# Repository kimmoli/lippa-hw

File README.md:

LIPPA
=====

* Powering 7.4V 2.5Ah lipo
* PCB Size 80x50 mm, M3 mounting holes at corners 3.5/3.5
* 4 stepper motor drivers
* 3 servo drivers
* CPU STM32
  * UART for Lidar
  * Debug UART
  * USB VCP
  * 3 timers for servo
  * 4 timers for stepper
  * 4 GPIO to control servo directions
  * 4 GPIO to control servo enables
  * 4 GPIO to control servo microstep modes
  * SPI for PS2 controller

Parts
===== 
* CPU [STM32F417VE](http://www.st.com/content/ccc/resource/technical/document/datasheet/98/9f/89/73/01/b1/48/98/DM00035129.pdf/files/DM00035129.pdf/jcr:content/translations/en.DM00035129.pdf)
* Stepper drivers [DRV8834](http://www.ti.com/lit/ds/symlink/drv8834.pdf)
* Power supply [TPS561201](http://www.ti.com/lit/ds/symlink/tps561201.pdf)

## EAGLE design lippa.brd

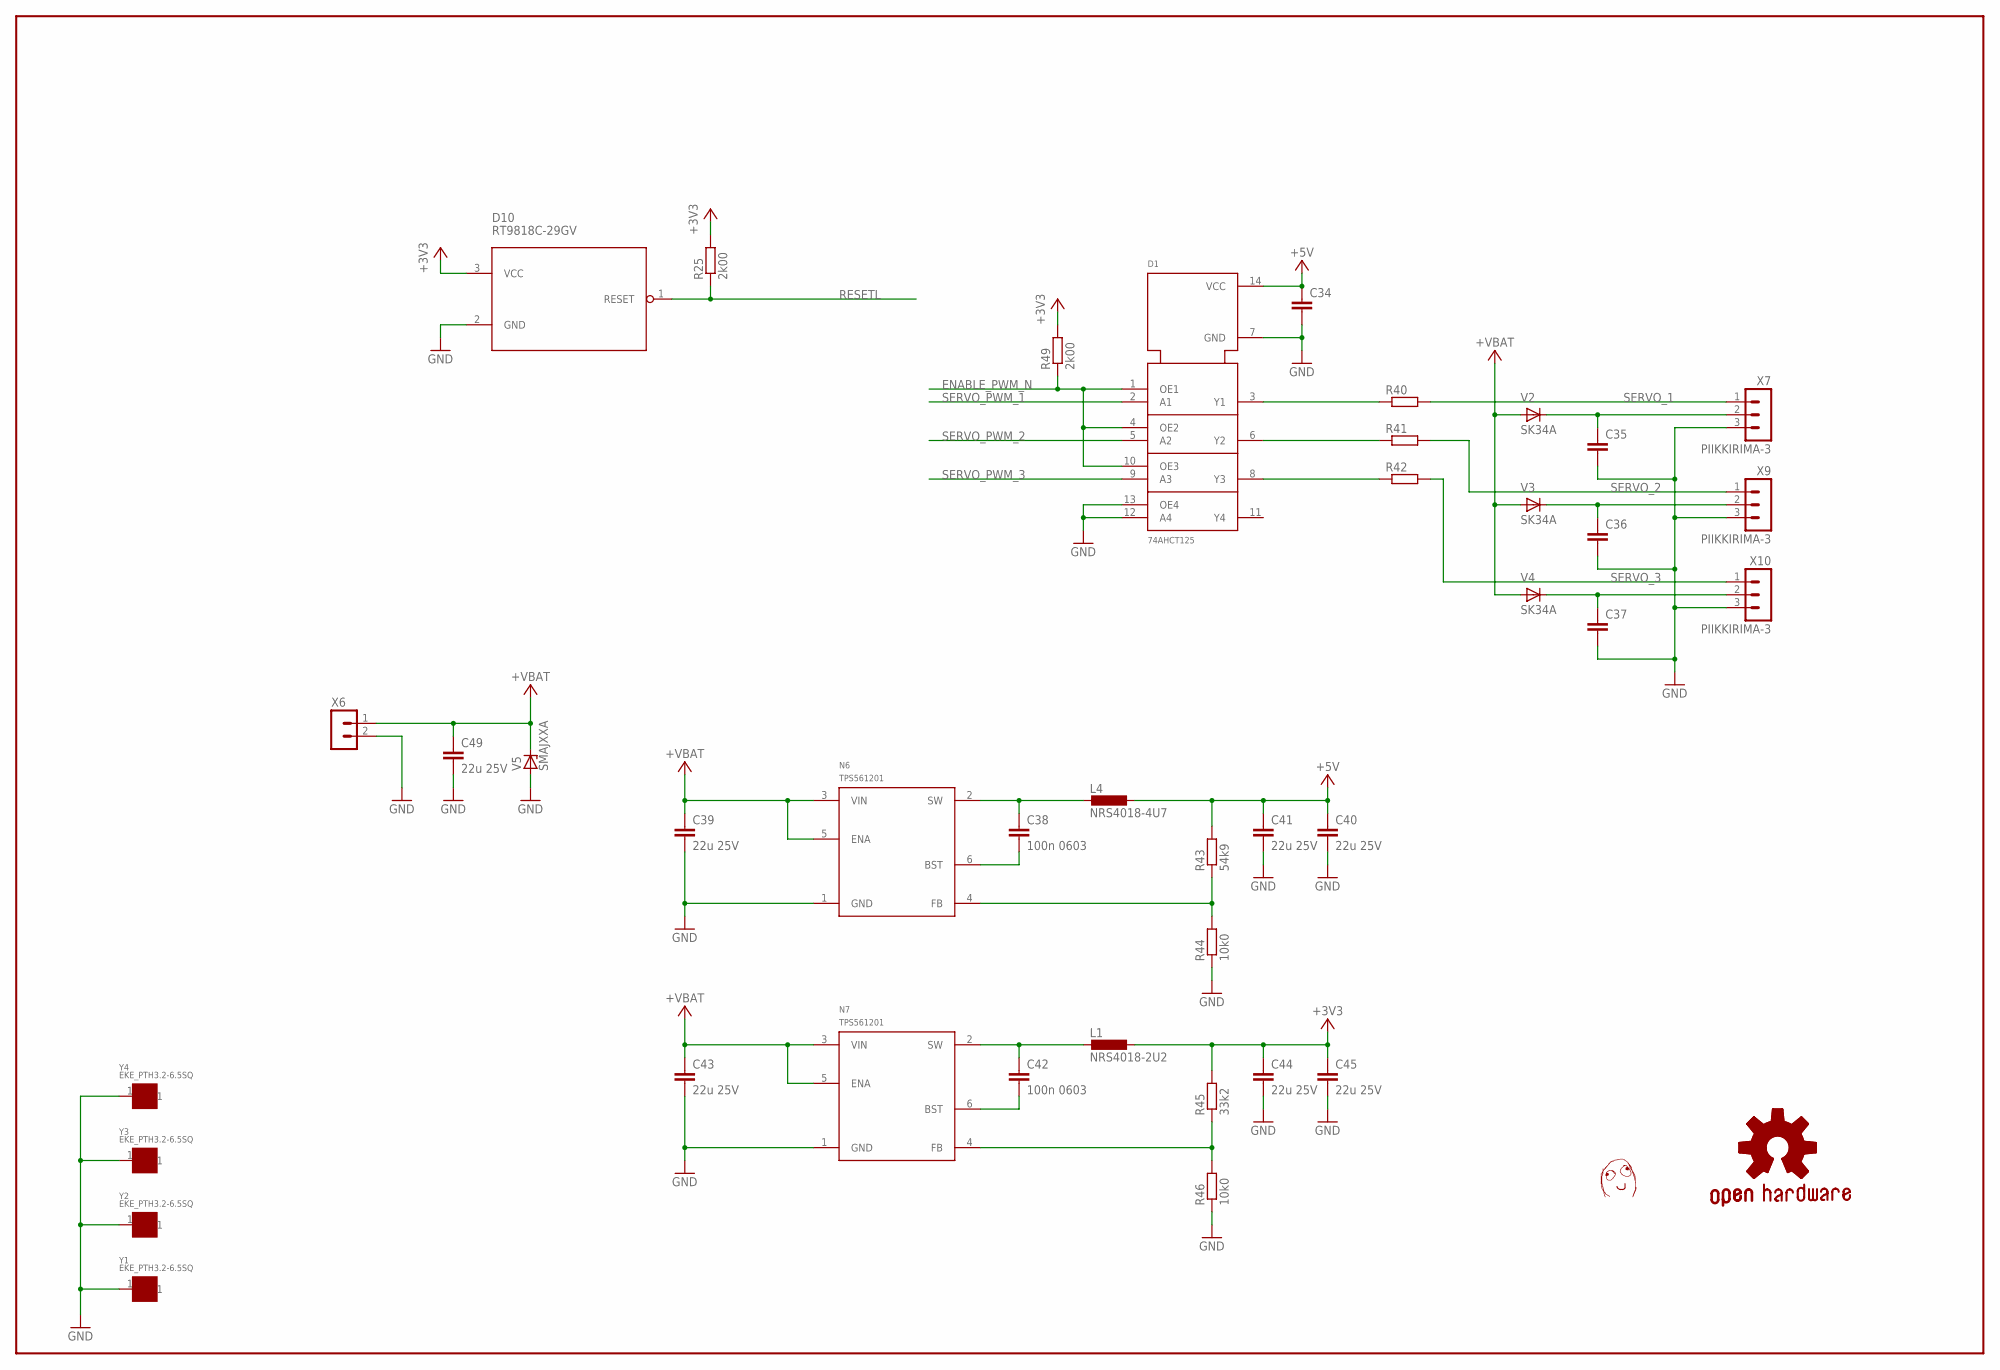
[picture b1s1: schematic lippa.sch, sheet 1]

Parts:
C34, C35, C36, C37: OMAT_IC_2_CAP0603; OMAT_IC_2_C0603
C38, C42: 100n 0603; OMAT_IC_2_C0603
C39, C40, C41, C43, C44, C45, C49: 22u 25V; OMAT_IC_2_C0805
D1: 74AHCT125; SO14
D10: RT9818C-29GV; SOT23
L1: NRS4018-2U2; NRS4018
L4: NRS4018-4U7; NRS4018
N6, N7: TPS561201; OMAT_IC_2_SOT23-6
R25, R49: 2k00; R0603
R40, R41, R42: OMAT_IC_2_RES0603; OMAT_IC_2_R0603
R43: 54k9; OMAT_IC_2_R0603
R44, R46: 10k0; OMAT_IC_2_R0603
R45: 33k2; OMAT_IC_2_R0603
U$1: DAFUG
V2, V3, V4: SK34A; OMAT_IC_2_DO214AC
V5: SMAJXXA; DO214AC
X6: TE_RUUVILIITIN2
X7, X9, X10: PIIKKIRIMA-3
Y1, Y2, Y3, Y4: EKE_PTH3.2-6.5SQ; EKE_PTH-3.2-6.5SQ

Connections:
+3V3: C44.1, C45.1, D10.3 (VCC), L1.1, R25.2, R45.2, R49.2; also elsewhere on the board
+5V: C34.1, C40.1, C41.1, D1.14 (VCC), L4.1, R43.2; also elsewhere on the board
+VBAT: C39.1, C43.1, C49.1, N6.3 (VIN), N6.5 (ENA), N7.3 (VIN), N7.5 (ENA), V2.A, V3.A, V4.A, V5.C, X6.1; also elsewhere on the board
ENABLE_PWM_N: D1.1 (OE1), D1.4 (OE2), D1.10 (OE3), R49.1; also elsewhere on the board
GND: C34.2, C35.2, C36.2, C37.2, C39.2, C40.2, C41.2, C43.2, C44.2, C45.2, C49.2, D1.7 (GND), D1.12 (A4), D1.13 (OE4), D10.2 (GND), N6.1 (GND), N7.1 (GND), R44.1, R46.1, V5.A, X6.2, X7.3, X9.3, X10.3, Y1.1, Y2.1, Y3.1, Y4.1; also elsewhere on the board
unnamed: D1.3 (Y1), R40.1
unnamed: D1.6 (Y2), R41.1
unnamed: D1.8 (Y3), R42.1
unnamed: C38.1, L4.2, N6.2 (SW)
unnamed: C37.1, V4.C, X10.2
unnamed: C36.1, V3.C, X9.2
unnamed: C35.1, V2.C, X7.2
unnamed: C38.2, N6.6 (BST)
unnamed: N6.4 (FB), R43.1, R44.2
unnamed: C42.1, L1.2, N7.2 (SW)
unnamed: C42.2, N7.6 (BST)
unnamed: N7.4 (FB), R45.1, R46.2
RESETL: D10.1 (RESET), R25.1; also elsewhere on the board
SERVO_1: R40.2, X7.1
SERVO_2: R41.2, X9.1
SERVO_3: R42.2, X10.1
SERVO_PWM_1: D1.2 (A1); also elsewhere on the board
SERVO_PWM_2: D1.5 (A2); also elsewhere on the board
SERVO_PWM_3: D1.9 (A3); also elsewhere on the board

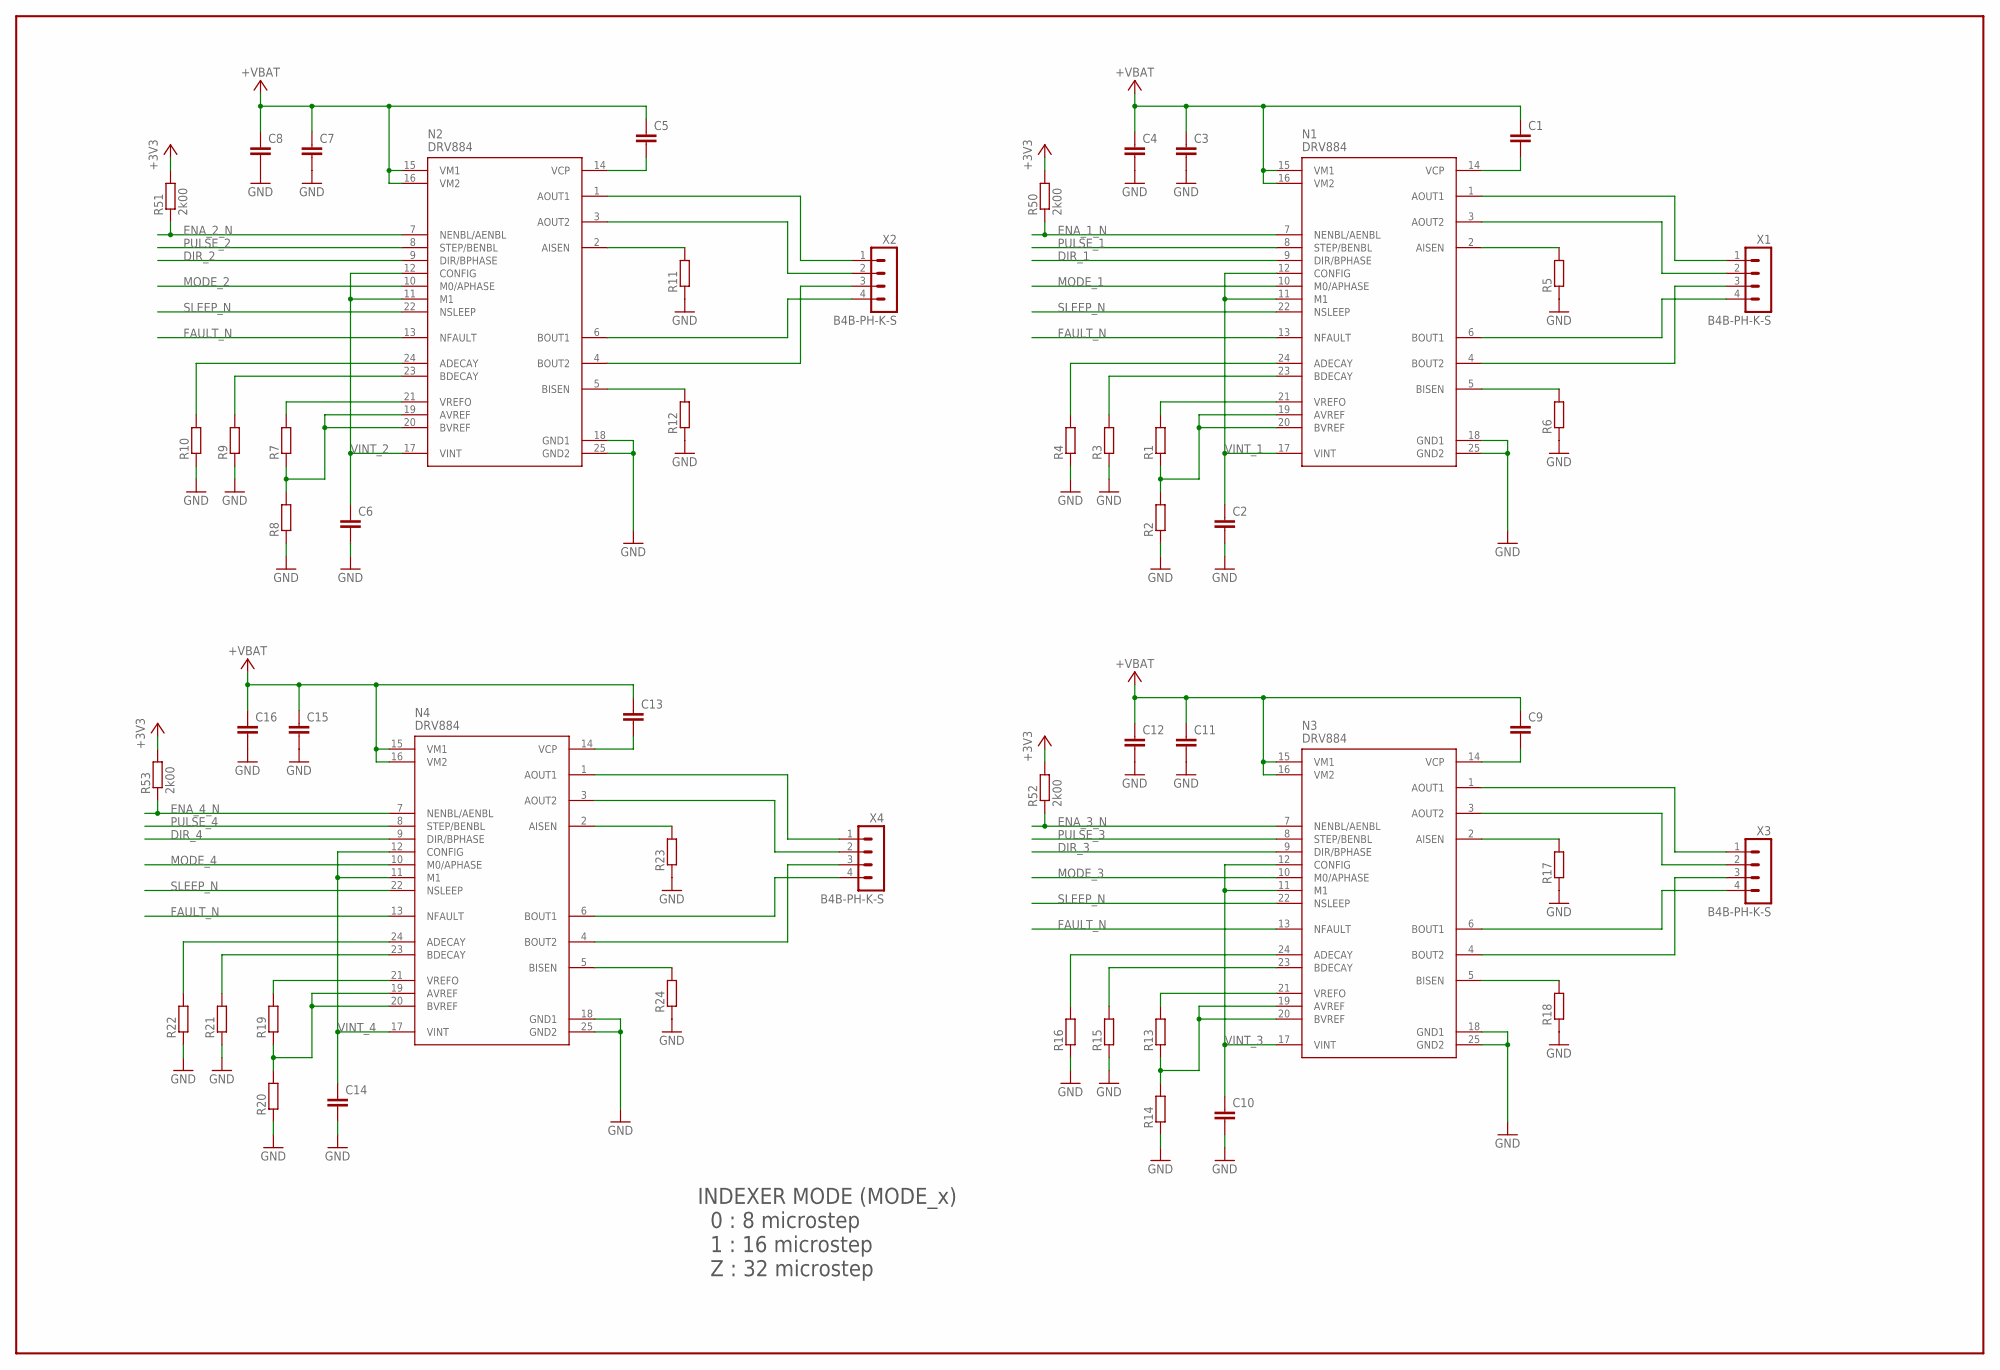
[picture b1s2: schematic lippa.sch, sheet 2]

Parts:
C1, C2, C3, C5, C6, C7, C9, C10, C11, C13, C14, C15: OMAT_IC_2_CAP0603; OMAT_IC_2_C0603
C4, C8, C12, C16: OMAT_IC_2_CAP0805; OMAT_IC_2_C0805
N1, N2, N3, N4: DRV884; QFN50P400X400X100-25N
R1, R2, R3, R4, R7, R8, R9, R10, R13, R14, R15, R16, R19, R20, R21, R22: OMAT_IC_2_RES0603; OMAT_IC_2_R0603
R5, R6, R11, R12, R17, R18, R23, R24: OMAT_IC_2_RES1206; OMAT_IC_2_R1206
R50, R51, R52, R53: 2k00; R0603
X1, X2, X3, X4: B4B-PH-K-S

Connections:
+3V3: R50.2, R51.2, R52.2, R53.2; also elsewhere on the board
+VBAT: C1.1, C3.1, C4.1, C5.1, C7.1, C8.1, C9.1, C11.1, C12.1, C13.1, C15.1, C16.1, N1.15 (VM1), N1.16 (VM2), N2.15 (VM1), N2.16 (VM2), N3.15 (VM1), N3.16 (VM2), N4.15 (VM1), N4.16 (VM2); also elsewhere on the board
DIR_1: N1.9 (DIR/BPHASE); also elsewhere on the board
DIR_2: N2.9 (DIR/BPHASE); also elsewhere on the board
DIR_3: N3.9 (DIR/BPHASE); also elsewhere on the board
DIR_4: N4.9 (DIR/BPHASE); also elsewhere on the board
ENA_1_N: N1.7 (NENBL/AENBL), R50.1; also elsewhere on the board
ENA_2_N: N2.7 (NENBL/AENBL), R51.1; also elsewhere on the board
ENA_3_N: N3.7 (NENBL/AENBL), R52.1; also elsewhere on the board
ENA_4_N: N4.7 (NENBL/AENBL), R53.1; also elsewhere on the board
FAULT_N: N1.13 (NFAULT), N2.13 (NFAULT), N3.13 (NFAULT), N4.13 (NFAULT); also elsewhere on the board
GND: C2.2, C3.2, C4.2, C6.2, C7.2, C8.2, C10.2, C11.2, C12.2, C14.2, C15.2, C16.2, N1.18 (GND1), N1.25 (GND2), N2.18 (GND1), N2.25 (GND2), N3.18 (GND1), N3.25 (GND2), N4.18 (GND1), N4.25 (GND2), R2.1, R3.1, R4.1, R5.1, R6.1, R8.1, R9.1, R10.1, R11.1, R12.1, R14.1, R15.1, R16.1, R17.1, R18.1, R20.1, R21.1, R22.1, R23.1, R24.1; also elsewhere on the board
MODE_1: N1.10 (M0/APHASE); also elsewhere on the board
MODE_2: N2.10 (M0/APHASE); also elsewhere on the board
MODE_3: N3.10 (M0/APHASE); also elsewhere on the board
MODE_4: N4.10 (M0/APHASE); also elsewhere on the board
unnamed: C1.2, N1.14 (VCP)
unnamed: N1.24 (ADECAY), R4.2
unnamed: N1.21 (VREFO), R1.2
unnamed: N1.19 (AVREF), N1.20 (BVREF), R1.1, R2.2
unnamed: N1.23 (BDECAY), R3.2
unnamed: N1.2 (AISEN), R5.2
unnamed: N1.5 (BISEN), R6.2
unnamed: N1.6 (BOUT1), X1.4
unnamed: N1.4 (BOUT2), X1.3
unnamed: N1.1 (AOUT1), X1.1
unnamed: N1.3 (AOUT2), X1.2
unnamed: C5.2, N2.14 (VCP)
unnamed: N2.21 (VREFO), R7.2
unnamed: N2.19 (AVREF), N2.20 (BVREF), R7.1, R8.2
unnamed: N2.24 (ADECAY), R10.2
unnamed: N2.23 (BDECAY), R9.2
unnamed: N2.2 (AISEN), R11.2
unnamed: N2.5 (BISEN), R12.2
unnamed: N2.6 (BOUT1), X2.4
unnamed: N2.4 (BOUT2), X2.3
unnamed: N2.1 (AOUT1), X2.1
unnamed: N2.3 (AOUT2), X2.2
unnamed: C9.2, N3.14 (VCP)
unnamed: N3.21 (VREFO), R13.2
unnamed: N3.19 (AVREF), N3.20 (BVREF), R13.1, R14.2
unnamed: N3.24 (ADECAY), R16.2
unnamed: N3.23 (BDECAY), R15.2
unnamed: N3.2 (AISEN), R17.2
unnamed: N3.5 (BISEN), R18.2
unnamed: N3.6 (BOUT1), X3.4
unnamed: N3.4 (BOUT2), X3.3
unnamed: N3.1 (AOUT1), X3.1
unnamed: N3.3 (AOUT2), X3.2
unnamed: C13.2, N4.14 (VCP)
unnamed: N4.21 (VREFO), R19.2
unnamed: N4.19 (AVREF), N4.20 (BVREF), R19.1, R20.2
unnamed: N4.24 (ADECAY), R22.2
unnamed: N4.23 (BDECAY), R21.2
unnamed: N4.2 (AISEN), R23.2
unnamed: N4.5 (BISEN), R24.2
unnamed: N4.6 (BOUT1), X4.4
unnamed: N4.4 (BOUT2), X4.3
unnamed: N4.1 (AOUT1), X4.1
unnamed: N4.3 (AOUT2), X4.2
PULSE_1: N1.8 (STEP/BENBL); also elsewhere on the board
PULSE_2: N2.8 (STEP/BENBL); also elsewhere on the board
PULSE_3: N3.8 (STEP/BENBL); also elsewhere on the board
PULSE_4: N4.8 (STEP/BENBL); also elsewhere on the board
SLEEP_N: N1.22 (NSLEEP), N2.22 (NSLEEP), N3.22 (NSLEEP), N4.22 (NSLEEP); also elsewhere on the board
VINT_1: C2.1, N1.11 (M1), N1.12 (CONFIG), N1.17 (VINT)
VINT_2: C6.1, N2.11 (M1), N2.12 (CONFIG), N2.17 (VINT)
VINT_3: C10.1, N3.11 (M1), N3.12 (CONFIG), N3.17 (VINT)
VINT_4: C14.1, N4.11 (M1), N4.12 (CONFIG), N4.17 (VINT)

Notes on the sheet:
INDEXER MODE (MODE_x) 0 : 8 microstep 1 : 16 microstep Z : 32 microstep

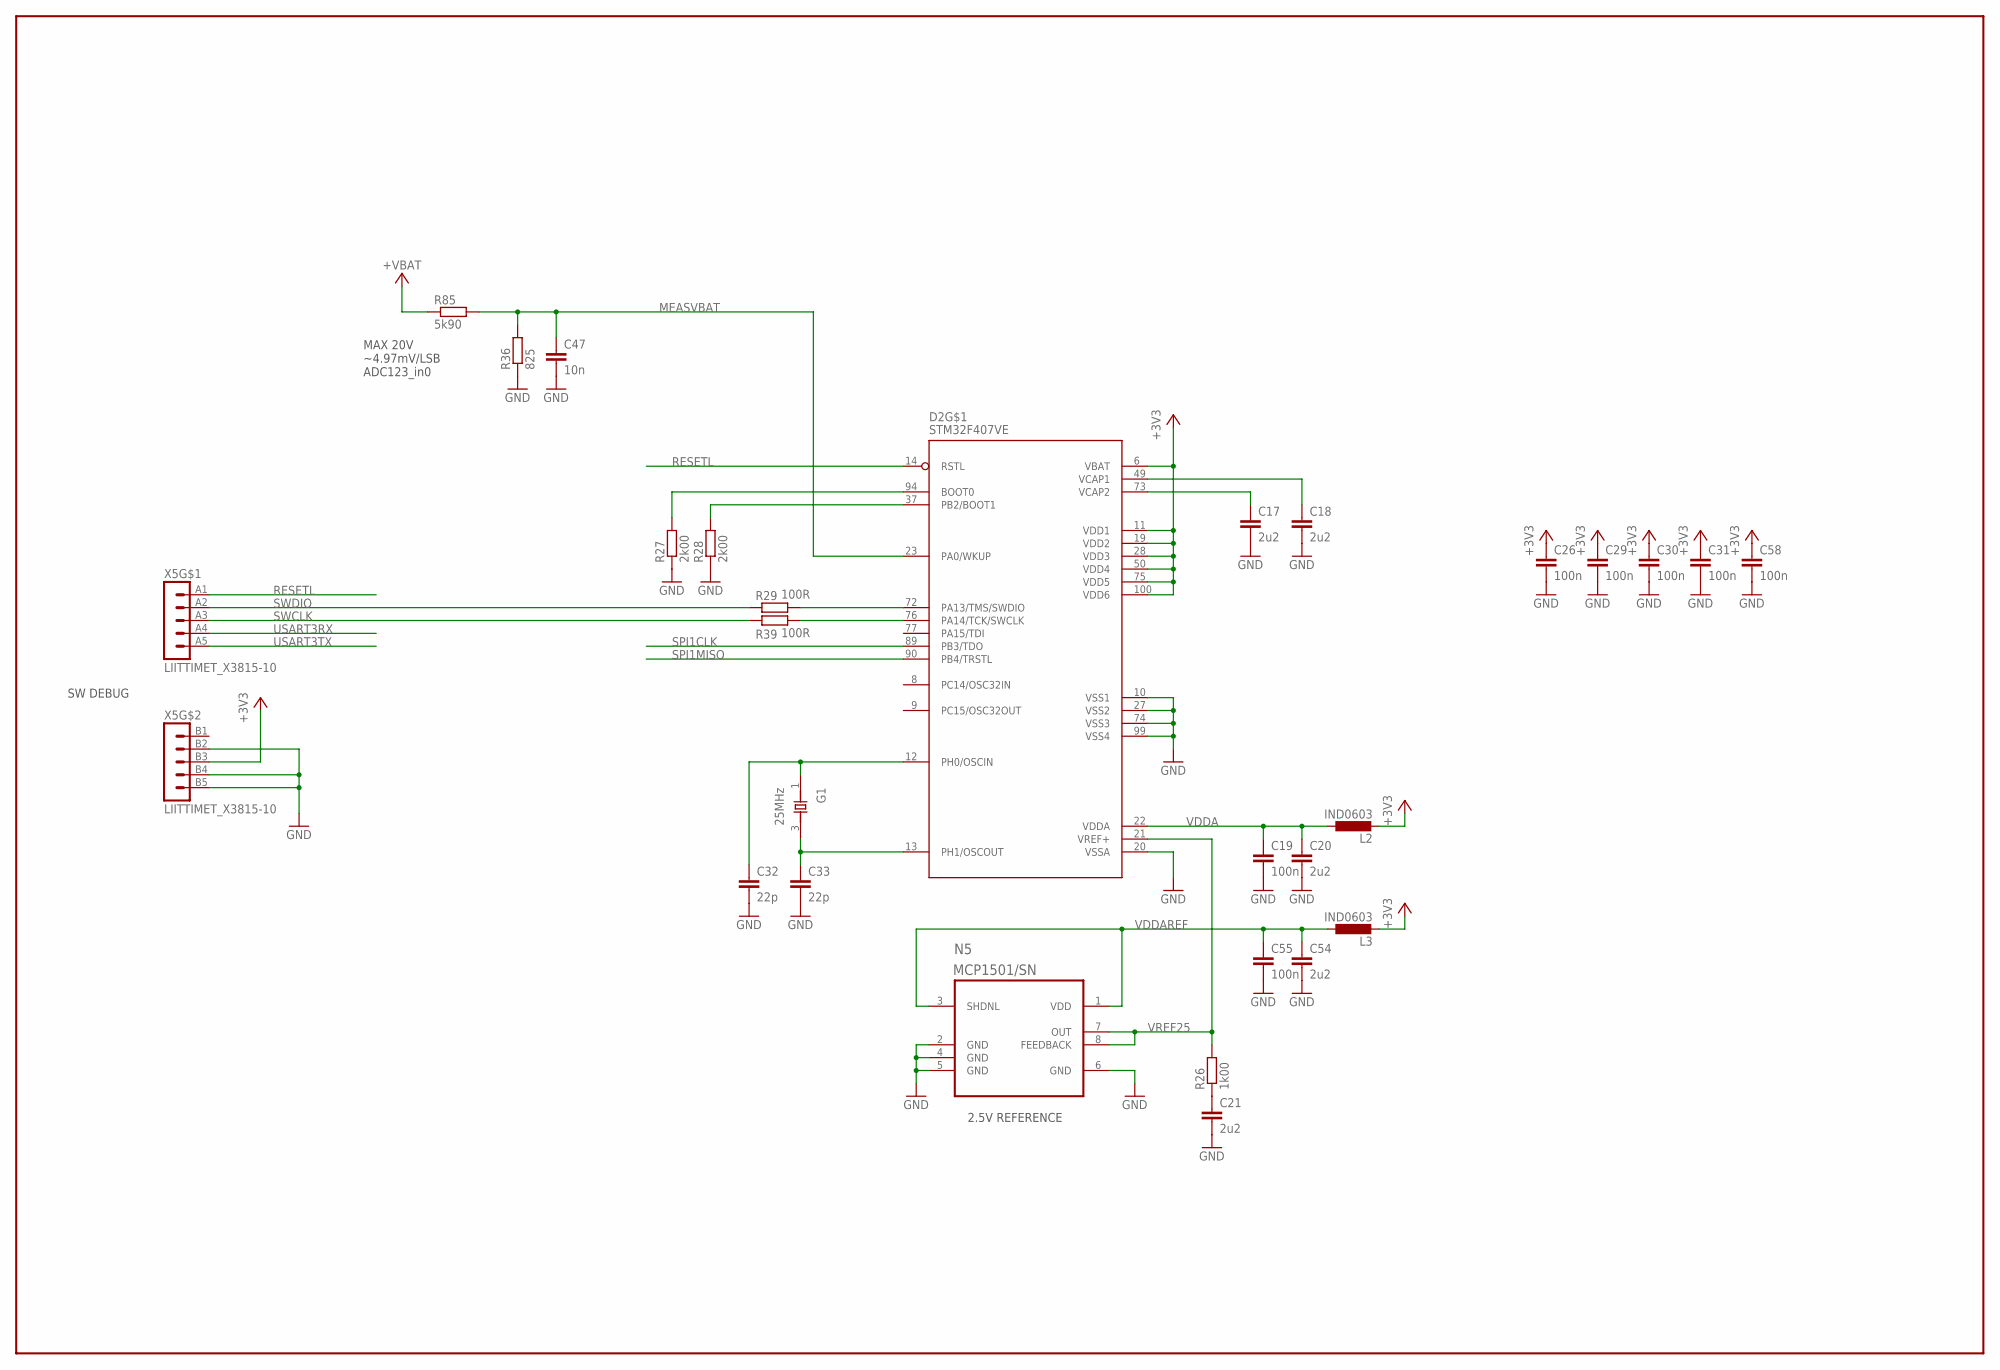
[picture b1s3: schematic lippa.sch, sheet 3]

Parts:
C17, C18, C20, C21, C54: 2u2; C0603
C19, C26, C29, C30, C31, C55, C58: 100n; C0603
C32, C33: 22p; C0603
C47: 10n; C0603
D2: STM32F407VE; LQFP-100
G1: 25MHz; X_3225
L2, L3: IND0603; R0603
N5: MCP1501/SN; SOIC8-N_MC
R26: 1k00; R0603
R27, R28: 2k00; R0603
R29, R39: 100R; PASSIIVIT_R0603
R36: 825; R0603
R85: 5k90; R0603
X5: LIITTIMET_X3815-10; LIITTIMET_15110102601

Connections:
+3V3: C26.1, C29.1, C30.1, C31.1, C58.1, D2.6 (VBAT), D2.11 (VDD1), D2.19 (VDD2), D2.28 (VDD3), D2.50 (VDD4), D2.75 (VDD5), D2.100 (VDD6), L2.2, L3.2, X5.B3 (3); also elsewhere on the board
+VBAT: R85.1; also elsewhere on the board
BOOT0: D2.94 (BOOT0), R27.2
BOOT1: D2.37 (PB2/BOOT1), R28.2
GND: C17.2, C18.2, C19.2, C20.2, C21.2, C26.2, C29.2, C30.2, C31.2, C32.2, C33.2, C47.2, C54.2, C55.2, C58.2, D2.10 (VSS1), D2.20 (VSSA), D2.27 (VSS2), D2.74 (VSS3), D2.99 (VSS4), N5.2 (GND), N5.4 (GND), N5.5 (GND), N5.6 (GND), R27.1, R28.1, R36.1, X5.B2 (2), X5.B4 (4), X5.B5 (5); also elsewhere on the board
MEASVBAT: C47.1, D2.23 (PA0/WKUP), R36.2, R85.2
unnamed: C21.1, R26.1
OSCIN: C32.1, D2.12 (PH0/OSCIN), G1.1 (X1)
OSCOUT: C33.1, D2.13 (PH1/OSCOUT), G1.3 (X2)
RESETL: D2.14 (RSTL), X5.A1 (1); also elsewhere on the board
SPI1CLK: D2.89 (PB3/TDO); also elsewhere on the board
SPI1MISO: D2.90 (PB4/TRSTL); also elsewhere on the board
SWCLK: R39.1, X5.A3 (3)
SWCLK_CPU: D2.76 (PA14/TCK/SWCLK), R39.2
SWDIO: R29.1, X5.A2 (2)
SWDIO_CPU: D2.72 (PA13/TMS/SWDIO), R29.2
USART3RX: X5.A4 (4); also elsewhere on the board
USART3TX: X5.A5 (5); also elsewhere on the board
VCAP1: C18.1, D2.49 (VCAP1)
VCAP2: C17.1, D2.73 (VCAP2)
VDDA: C19.1, C20.1, D2.22 (VDDA), L2.1
VDDAREF: C54.1, C55.1, L3.1, N5.1 (VDD), N5.3 (SHDNL)
VREF25: D2.21 (VREF+), N5.7 (OUT), N5.8 (FEEDBACK), R26.2

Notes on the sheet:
2.5V REFERENCE
SW DEBUG
MAX 20V ~4.97mV/LSB ADC123_in0

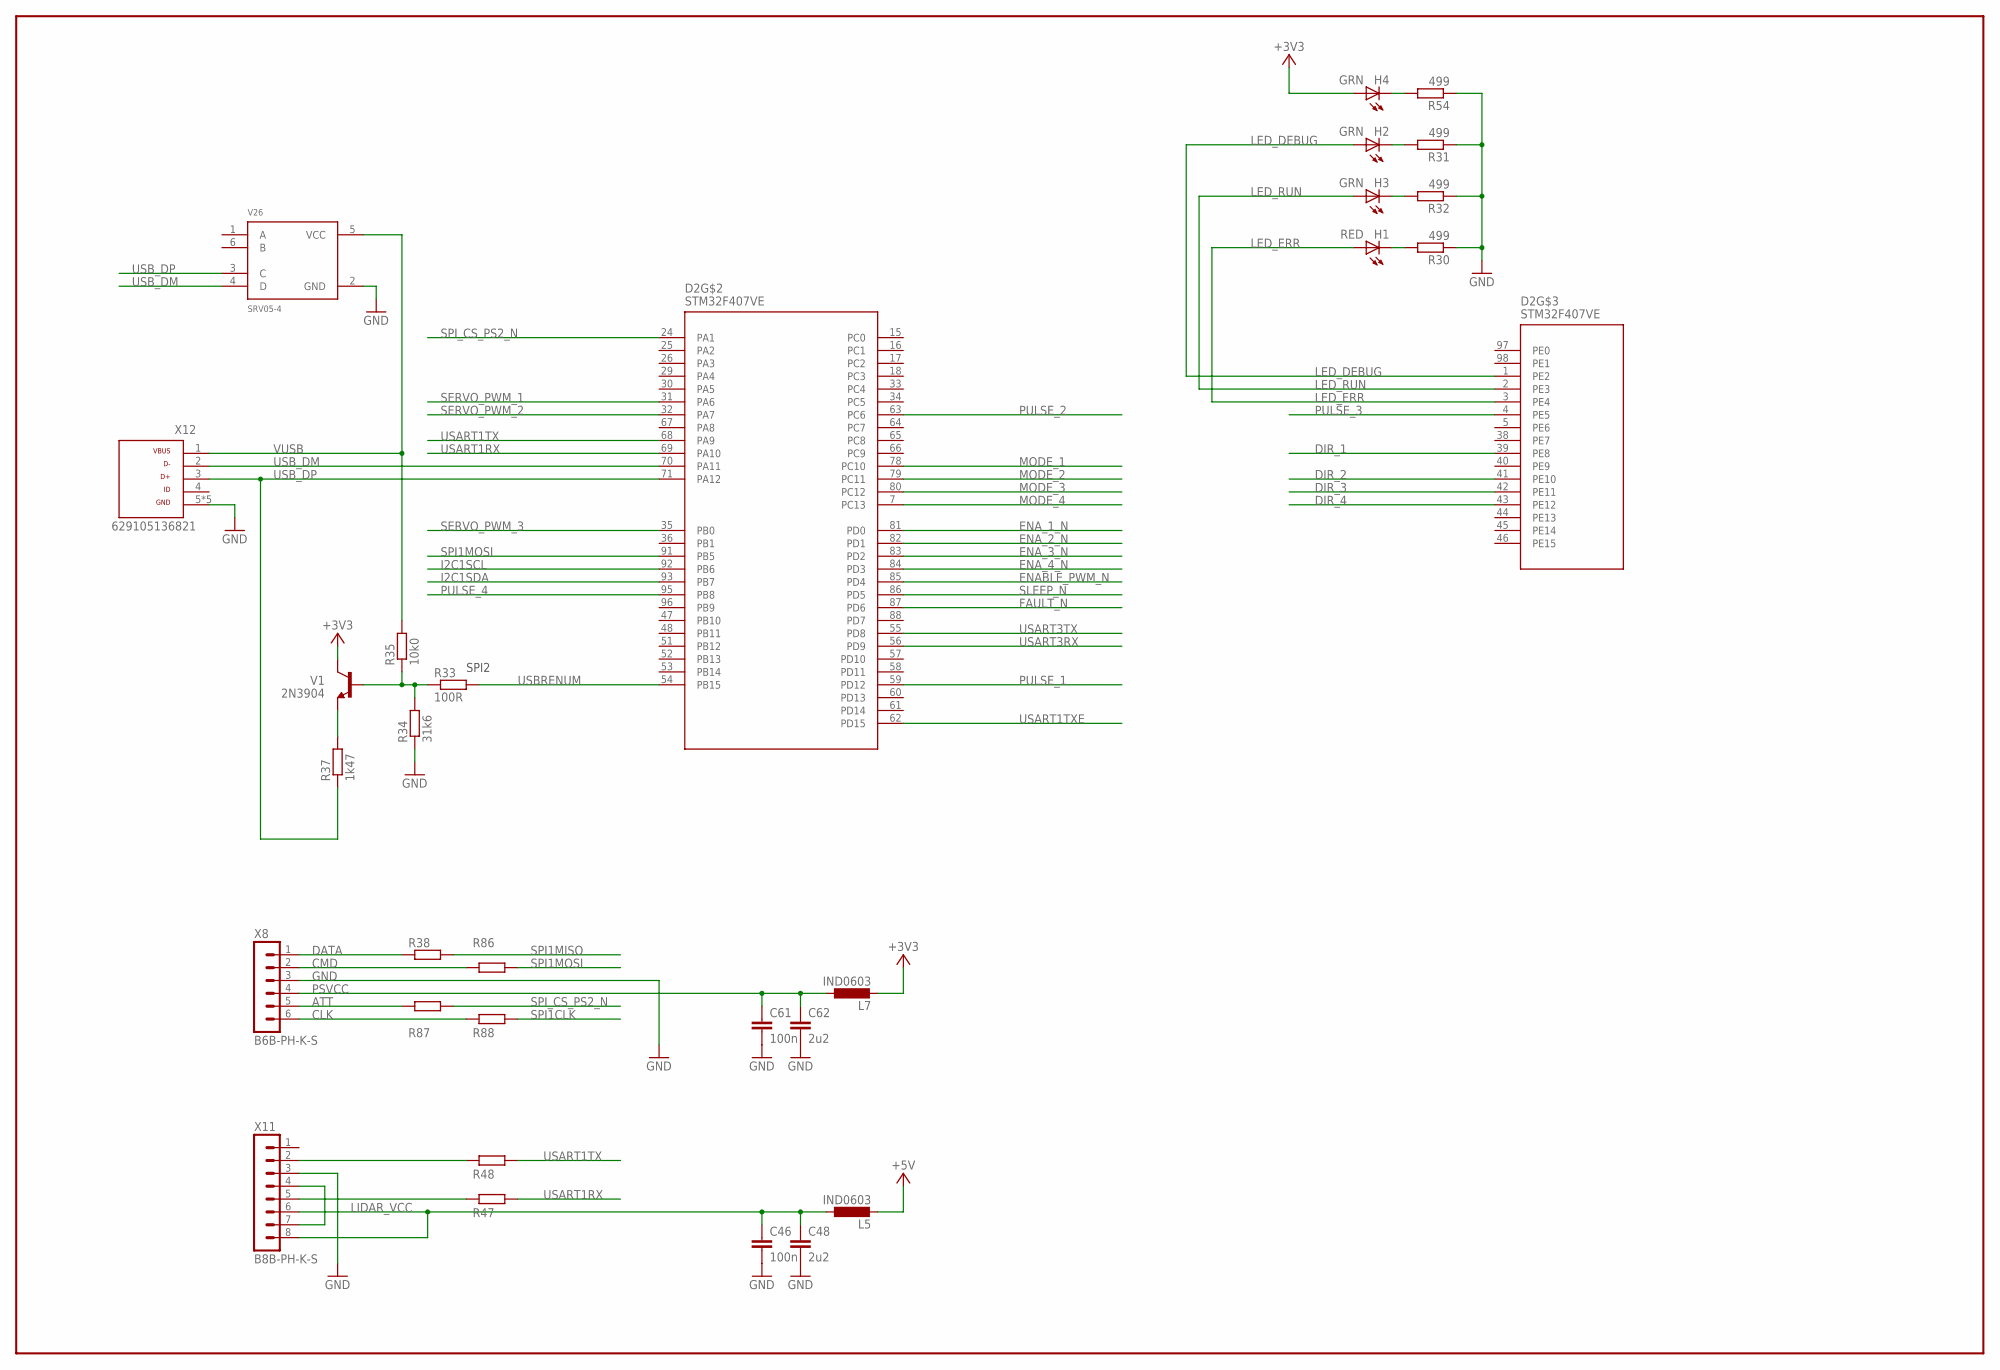
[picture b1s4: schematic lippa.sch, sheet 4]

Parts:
C46, C61: 100n; C0603
C48, C62: 2u2; C0603
D2: STM32F407VE; LQFP-100
H1: RED; CHIP-LED0603
H2, H3, H4: GRN; CHIP-LED0603
L5, L7: IND0603; R0603
R30, R31, R32, R54: 499; R0603
R33: 100R; PASSIIVIT_R0603
R34: 31k6; PASSIIVIT_R0603
R35: 10k0; PASSIIVIT_R0603
R37: 1k47; PASSIIVIT_R0603
R38, R47, R48, R86, R87, R88: RES0603; OMAT_IC_2_R0603
V1: 2N3904; OMAT_IC_2_SOT23
V26: SRV05-4; OMAT_IC_2_SOT23-6
X8: B6B-PH-K-S
X11: B8B-PH-K-S
X12: 629105136821

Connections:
+3V3: H4.A, L7.2, V1.3 (C); also elsewhere on the board
+5V: L5.2; also elsewhere on the board
ATT: R87.1, X8.5
CLK: R88.1, X8.6
CMD: R86.1, X8.2
DATA: R38.1, X8.1
DIR_1: D2.39 (PE8); also elsewhere on the board
DIR_2: D2.41 (PE10); also elsewhere on the board
DIR_3: D2.42 (PE11); also elsewhere on the board
DIR_4: D2.43 (PE12); also elsewhere on the board
ENABLE_PWM_N: D2.85 (PD4); also elsewhere on the board
ENA_1_N: D2.81 (PD0); also elsewhere on the board
ENA_2_N: D2.82 (PD1); also elsewhere on the board
ENA_3_N: D2.83 (PD2); also elsewhere on the board
ENA_4_N: D2.84 (PD3); also elsewhere on the board
FAULT_N: D2.87 (PD6); also elsewhere on the board
GND: C46.2, C48.2, C61.2, C62.2, R30.1, R31.1, R32.1, R34.1, R54.1, V26.2 (GND), X8.3, X11.3, X12.5, X12.Z1 (5), X12.Z2 (5), X12.Z3 (5), X12.Z4 (5); also elsewhere on the board
I2C1SCL: D2.92 (PB6)
I2C1SDA: D2.93 (PB7)
LED_DEBUG: D2.1 (PE2), H2.A
LED_ERR: D2.3 (PE4), H1.A
LED_RUN: D2.2 (PE3), H3.A
LIDAR_VCC: C46.1, C48.1, L5.1, X11.6, X11.8
MODE_1: D2.78 (PC10); also elsewhere on the board
MODE_2: D2.79 (PC11); also elsewhere on the board
MODE_3: D2.80 (PC12); also elsewhere on the board
MODE_4: D2.7 (PC13); also elsewhere on the board
unnamed: H4.C, R54.2
unnamed: H2.C, R31.2
unnamed: H1.C, R30.2
unnamed: H3.C, R32.2
unnamed: R33.1, R34.2, R35.1, V1.1 (B)
unnamed: R37.2, V1.2 (E)
unnamed: X11.4, X11.7
unnamed: R48.1, X11.2
unnamed: R47.1, X11.5
PSVCC: C61.1, C62.1, L7.1, X8.4
PULSE_1: D2.59 (PD12); also elsewhere on the board
PULSE_2: D2.63 (PC6); also elsewhere on the board
PULSE_3: D2.4 (PE5); also elsewhere on the board
PULSE_4: D2.95 (PB8); also elsewhere on the board
SERVO_PWM_1: D2.31 (PA6); also elsewhere on the board
SERVO_PWM_2: D2.32 (PA7); also elsewhere on the board
SERVO_PWM_3: D2.35 (PB0); also elsewhere on the board
SLEEP_N: D2.86 (PD5); also elsewhere on the board
SPI1CLK: R88.2; also elsewhere on the board
SPI1MISO: R38.2; also elsewhere on the board
SPI1MOSI: D2.91 (PB5), R86.2
SPI_CS_PS2_N: D2.24 (PA1), R87.2
USART1RX: D2.69 (PA10), R47.2
USART1TX: D2.68 (PA9), R48.2
USART1TXE: D2.62 (PD15)
USART3RX: D2.56 (PD9); also elsewhere on the board
USART3TX: D2.55 (PD8); also elsewhere on the board
USBRENUM: D2.54 (PB15), R33.2
USB_DM: D2.70 (PA11), V26.4 (D), X12.2
USB_DP: D2.71 (PA12), R37.1, V26.3 (C), X12.3
VUSB: R35.2, V26.5 (VCC), X12.1

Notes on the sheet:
SPI2

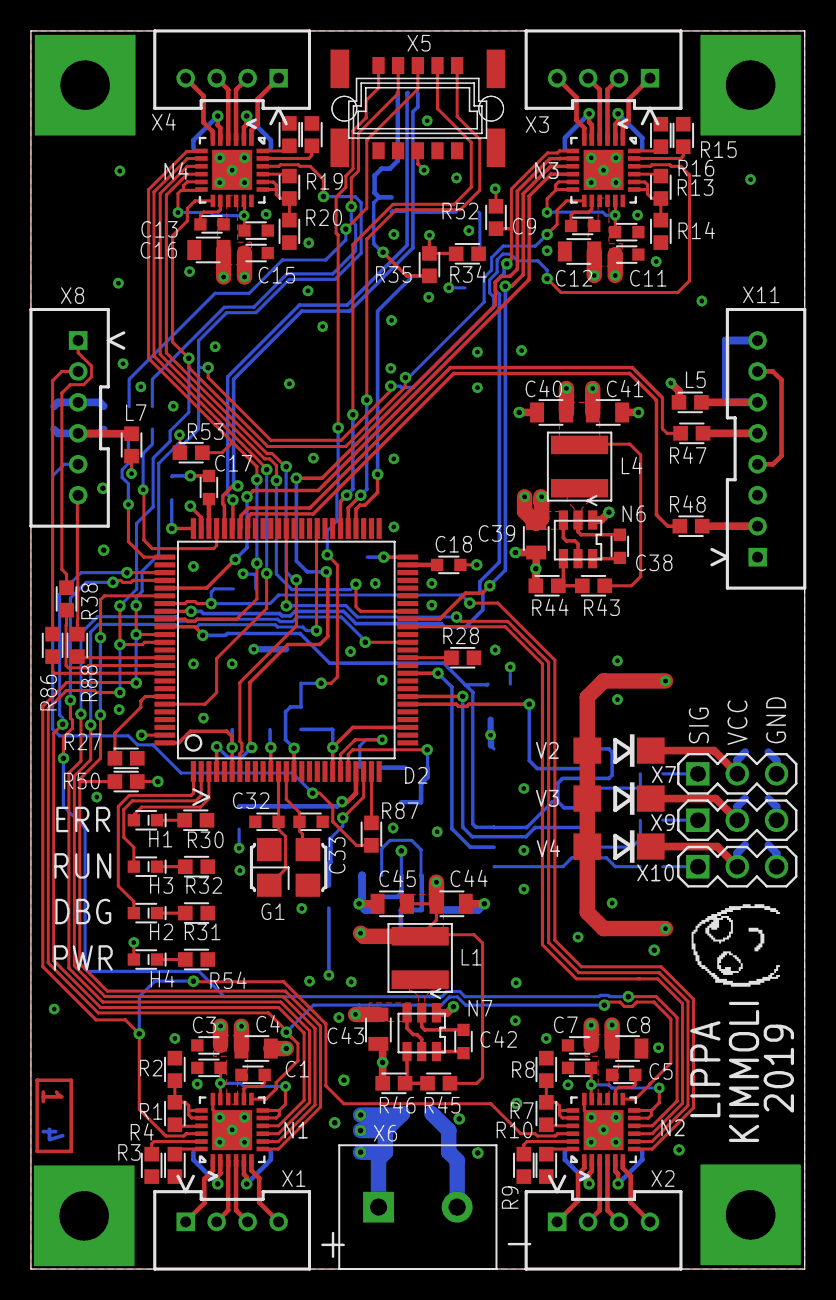
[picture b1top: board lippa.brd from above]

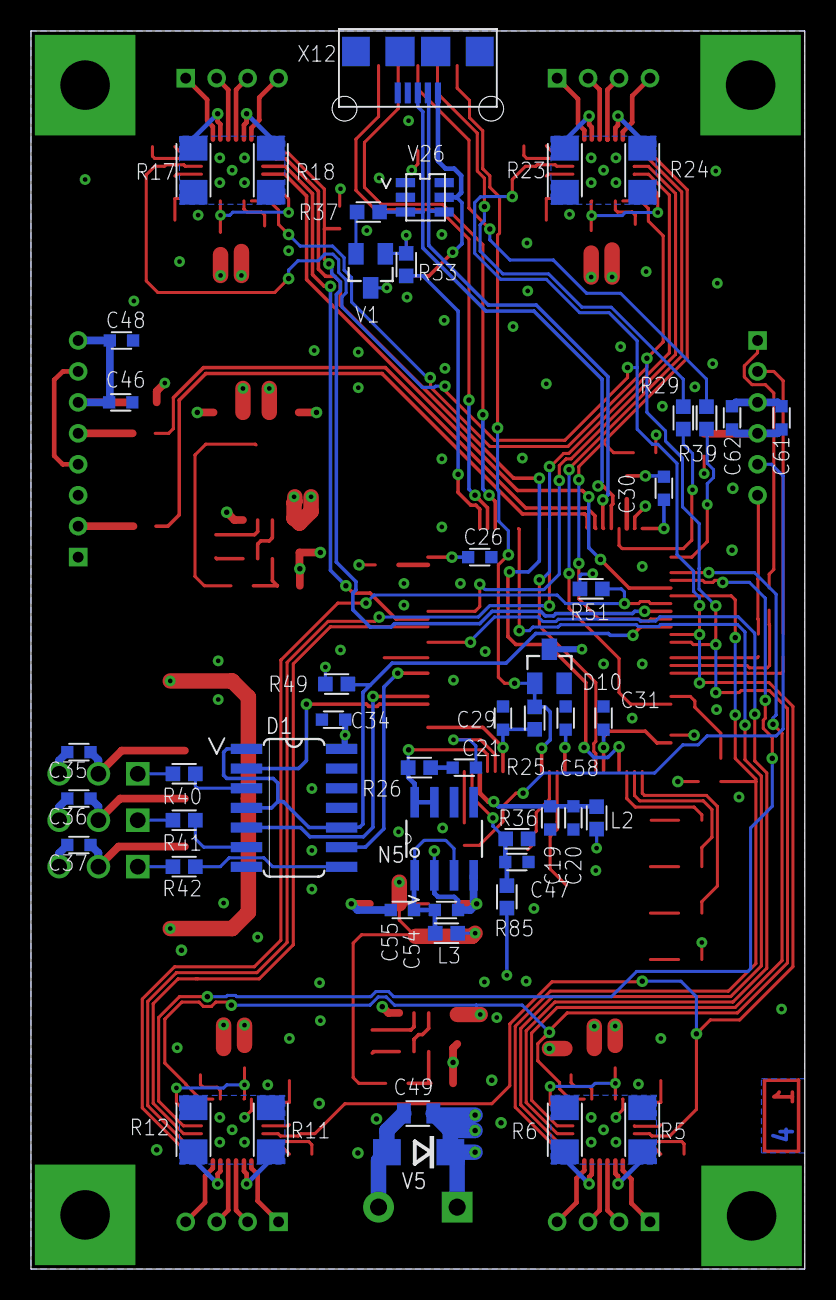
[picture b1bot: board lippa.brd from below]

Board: 4 copper layers, 50.0 x 80.0 mm, 150 parts (50 on the bottom side), 135 nets.

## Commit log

2019-04-22 initial
2019-04-25 initial design, nothing complete
2019-04-27 more wip
2019-04-27 almost done
2019-04-28 Layout complete
2019-04-28 Add documents
